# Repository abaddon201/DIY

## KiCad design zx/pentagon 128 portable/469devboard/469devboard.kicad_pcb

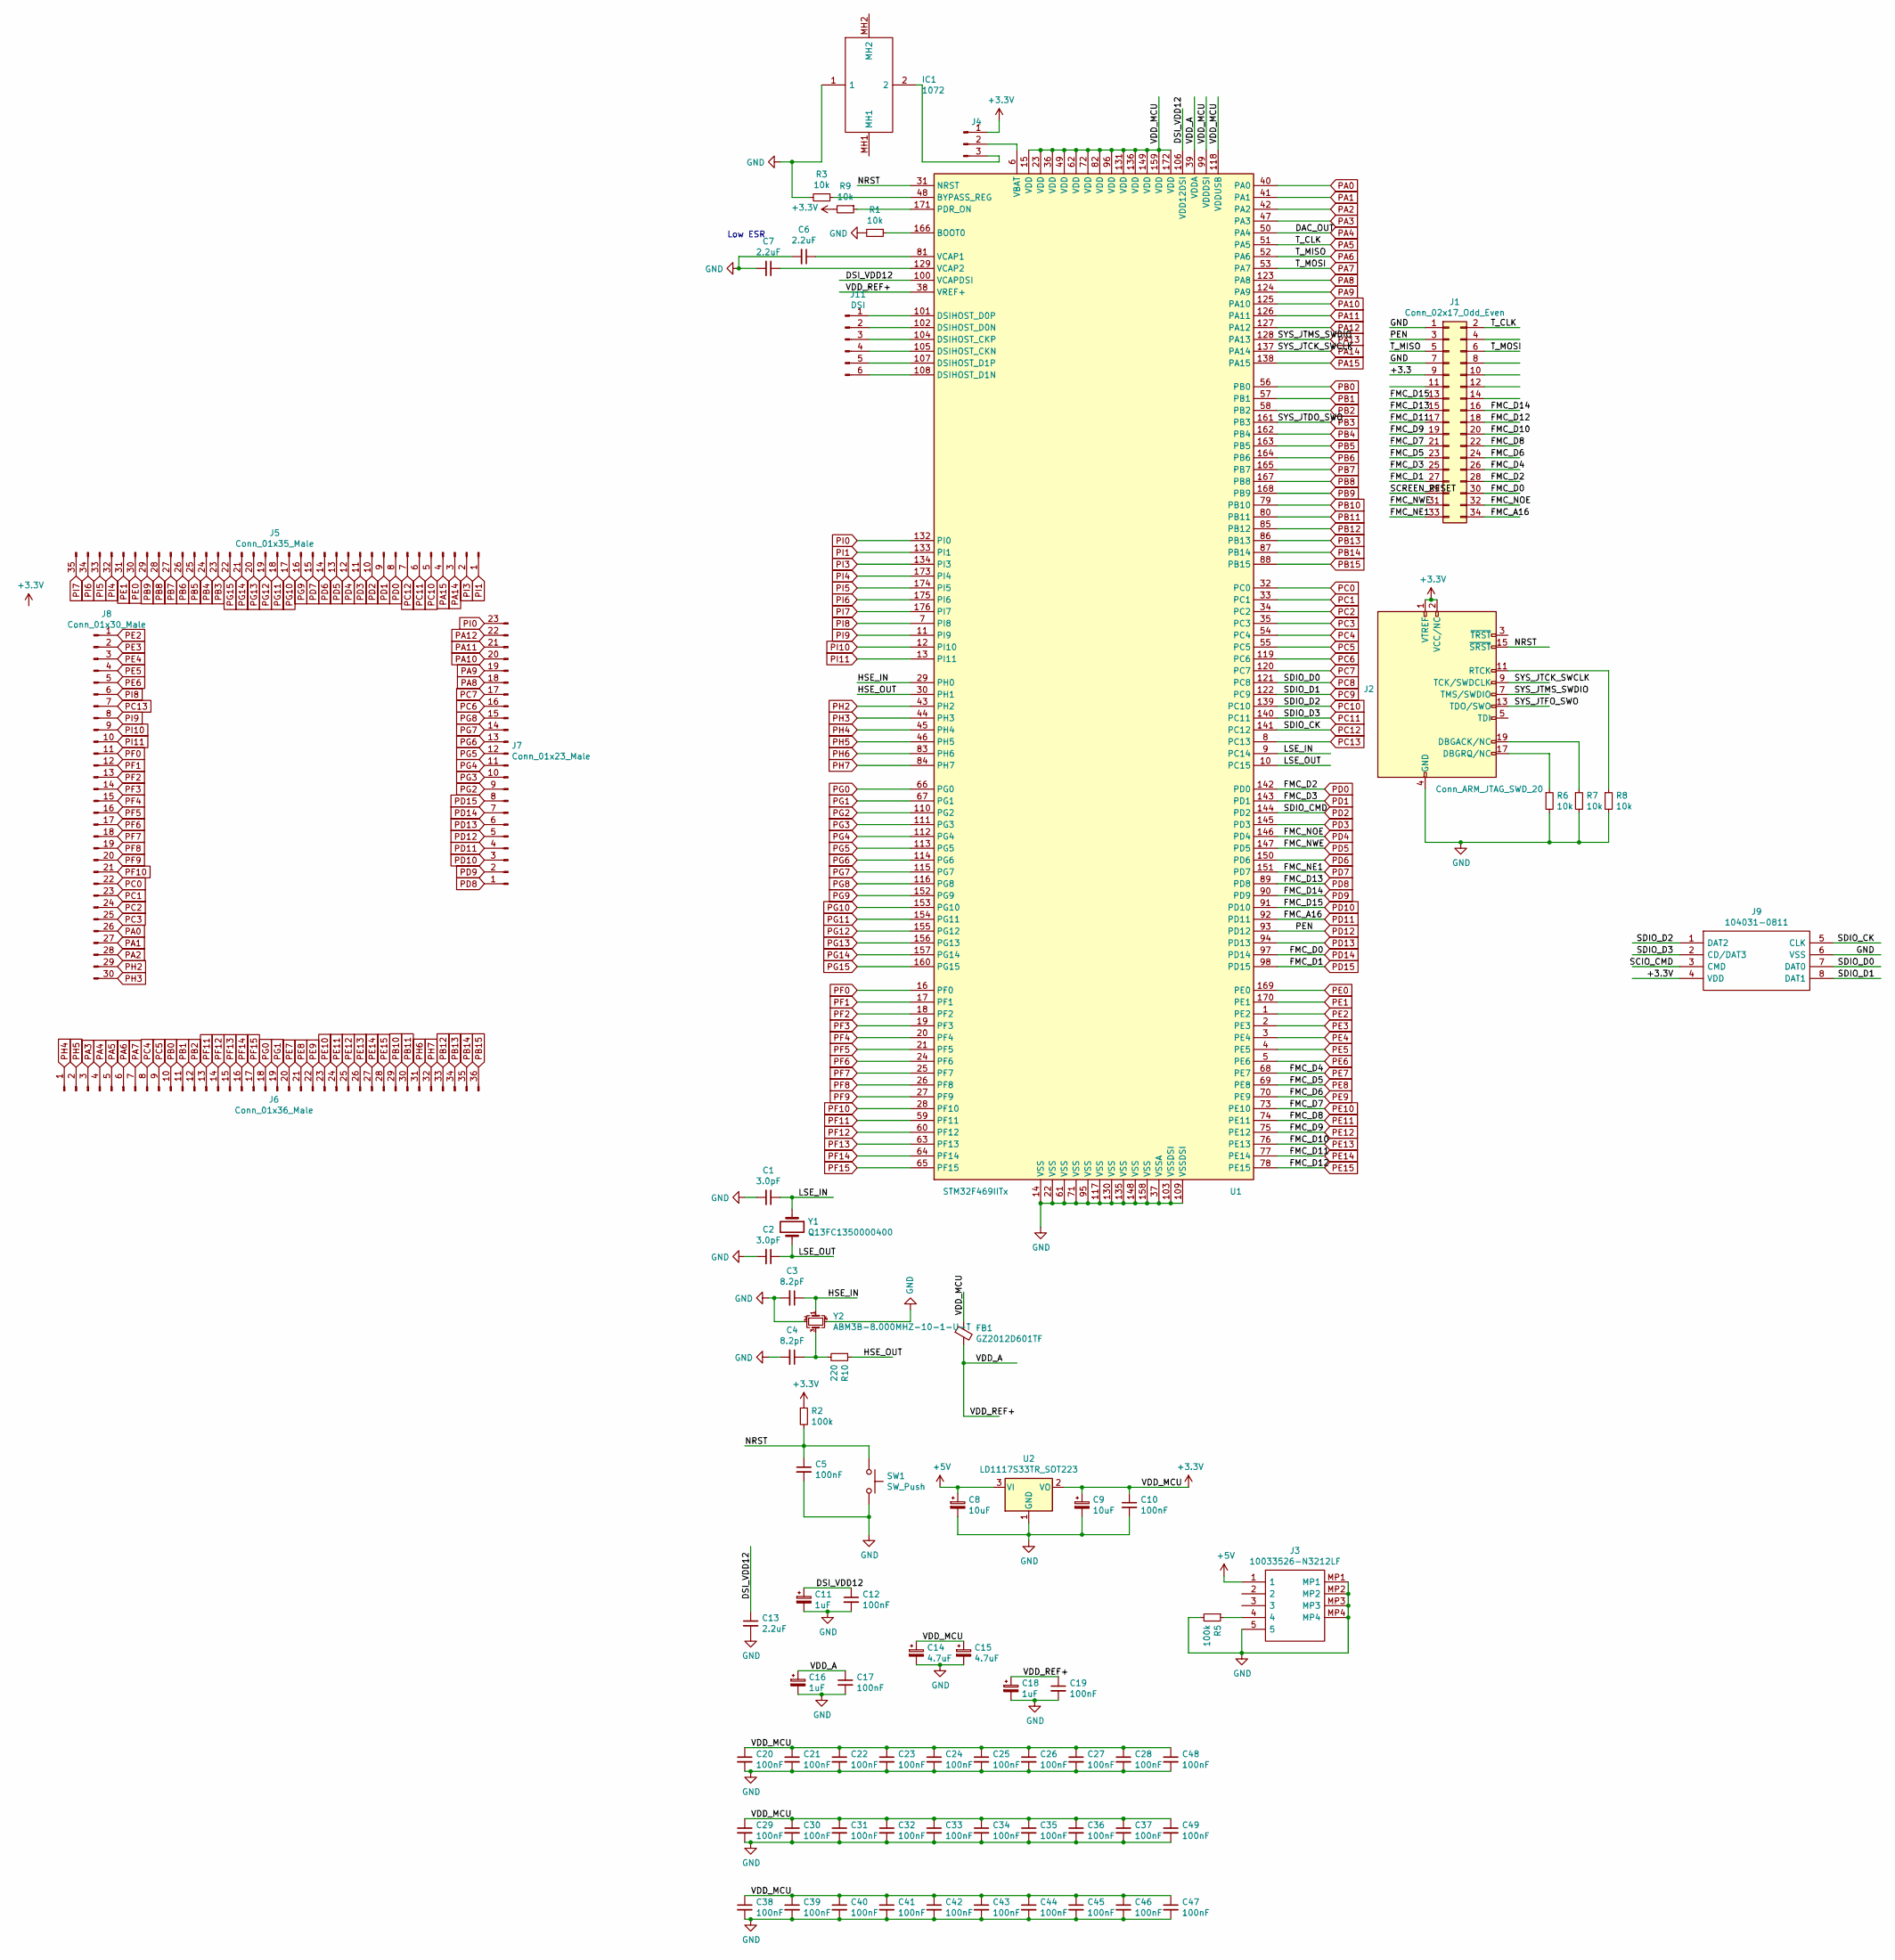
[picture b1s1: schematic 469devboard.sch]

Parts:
C1, C2: 3.0pF; C_0402_1005Metric
C3, C4: 8.2pF; C_0402_1005Metric
C5, C10, C12, C17, C19, C20, C21, C22, C23, C24, C25, C26, C27, C28, C29, C30, C31, C32, C33, C34, C35, C36, C37, C38, C39, C40, C41, C42, C43, C44, C45, C46, C47, C48, C49: 100nF; C_0402_1005Metric
C6, C7: 2.2uF; C_1210_3225Metric_Pad1.42x2.65mm_HandSolder
C8, C9: 10uF; C_0402_1005Metric
C11, C16, C18: 1uF; C_0402_1005Metric
C13: 2.2uF; C_0402_1005Metric
C14, C15: 4.7uF; C_0402_1005Metric
FB1: GZ2012D601TF; C_0805_2012Metric
IC1: 1072; Mouser Part Number 534-1072
J1: Conn_02x17_Odd_Even; PinSocket_2x17_P2.54mm_Vertical
J2: Conn_ARM_JTAG_SWD_20; PinHeader_2x10_P2.54mm_Vertical
J3: 10033526-N3212LF; 10033526N3212LF; Mouser Part Number 649-10033526-N3212LF
J4: Conn_01x03_Male; PinHeader_1x03_P2.54mm_Vertical
J5: Conn_01x35_Male; PinHeader_1x35_P2.54mm_Vertical
J6: Conn_01x36_Male; PinHeader_1x36_P2.54mm_Vertical
J7: Conn_01x23_Male; PinHeader_1x23_P2.54mm_Vertical
J8: Conn_01x30_Male; PinHeader_1x30_P2.54mm_Vertical
J9: 104031-0811; 1040310811; Mouser Part Number 538-104031-0811
J11: DSI; PinHeader_1x06_P2.54mm_Vertical
R1, R3, R6, R7, R8, R9: 10k; R_0402_1005Metric
R2, R5: 100k; R_0402_1005Metric
R10: 220; R_0402_1005Metric
SW1: SW_Push; SW_DIP_SPSTx01_Slide_6.7x4.1mm_W6.73mm_P2.54mm_LowProfile_J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
U1: STM32F469IITx; LQFP-176_24x24mm_P0.5mm
U2: LD1117S33TR_SOT223; SOT-223-3_TabPin2
Y1: Q13FC1350000400; Crystal_SMD_G8-2Pin_3.2x1.5mm
Y2: ABM3B-8.000MHZ-10-1-U-T; Crystal_SMD_Abracon_ABM3B-4Pin_5.0x3.2mm

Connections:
+3V3: C9.1, C10.1, C14.1, C15.1, C20.1, C21.1, C22.1, C23.1, C24.1, C25.1, C26.1, C27.1, C28.1, C29.1, C30.1, C31.1, C32.1, C33.1, C34.1, C35.1, C36.1, C37.1, C38.1, C39.1, C40.1, C41.1, C42.1, C43.1, C44.1, C45.1, C46.1, C47.1, C48.1, C49.1, FB1.1, J2.1 (VTREF), J2.2 (VCC/NC), J4.1, R2.1, R9.2, U1.15 (VDD), U1.23 (VDD), U1.36 (VDD), U1.49 (VDD), U1.62 (VDD), U1.72 (VDD), U1.82 (VDD), U1.96 (VDD), U1.99 (VDDDSI), U1.118 (VDDUSB), U1.131 (VDD), U1.136 (VDD), U1.149 (VDD), U1.159 (VDD), U1.172 (VDD), U2.2 (VO)
+5V: C8.1, J3.1, U2.3 (VI)
/DSI_VDD12: C11.1, C12.1, C13.1, U1.100 (VCAPDSI), U1.106 (VDD12DSI)
/HSE_IN: C3.1, U1.29 (PH0), Y2.1
/HSE_OUT: R10.1, U1.30 (PH1)
/LSE_IN: C1.1, U1.9 (PC14), Y1.1
/LSE_OUT: C2.1, U1.10 (PC15), Y1.2
/NRST: C5.1, J2.15 (~SRST~), R2.2, SW1.1, U1.31 (NRST)
/VDD_A: C16.1, C17.1, C18.1, C19.1, FB1.2, U1.38 (VREF+), U1.39 (VDDA)
GND: C1.2, C2.2, C3.2, C4.2, C5.2, C6.2, C7.2, C8.2, C9.2, C10.2, C11.2, C12.2, C13.2, C14.2, C15.2, C16.2, C17.2, C18.2, C19.2, C20.2, C21.2, C22.2, C23.2, C24.2, C25.2, C26.2, C27.2, C28.2, C29.2, C30.2, C31.2, C32.2, C33.2, C34.2, C35.2, C36.2, C37.2, C38.2, C39.2, C40.2, C41.2, C42.2, C43.2, C44.2, C45.2, C46.2, C47.2, C48.2, C49.2, IC1.1, J1.1, J1.7, J2.4 (GND), J2.6 (GND), J2.8 (GND), J2.10 (GND), J2.12 (GND), J2.14 (GND), J2.16 (GND), J2.18 (GND), J2.20 (GND), J3.5, J3.MP1, J3.MP2, J3.MP3, J3.MP4, J9.6 (VSS), R1.2, R3.2, R5.2, R6.2, R7.2, R8.2, SW1.2, U1.14 (VSS), U1.22 (VSS), U1.37 (VSSA), U1.61 (VSS), U1.71 (VSS), U1.95 (VSS), U1.103 (VSSDSI), U1.109 (VSSDSI), U1.117 (VSS), U1.130 (VSS), U1.135 (VSS), U1.148 (VSS), U1.158 (VSS), U2.1 (GND), Y2.2, Y2.4
unnamed: C4.1, R10.2, Y2.3
unnamed: C6.1, U1.81 (VCAP1)
unnamed: C7.1, U1.129 (VCAP2)
unnamed: IC1.2, J4.3
unnamed: J2.11 (RTCK), R8.1
unnamed: J2.17 (DBGRQ/NC), R6.1
unnamed: J2.19 (DBGACK/NC), R7.1
unnamed: J3.4, R5.1
unnamed: J4.2, U1.6 (VBAT)
unnamed: J11.1, U1.101 (DSIHOST_D0P)
unnamed: J11.2, U1.102 (DSIHOST_D0N)
unnamed: J11.3, U1.104 (DSIHOST_CKP)
unnamed: J11.4, U1.105 (DSIHOST_CKN)
unnamed: J11.5, U1.107 (DSIHOST_D1P)
unnamed: J11.6, U1.108 (DSIHOST_D1N)
unnamed: R1.1, U1.166 (BOOT0)
unnamed: R3.1, U1.48 (BYPASS_REG)
unnamed: R9.1, U1.171 (PDR_ON)
PA0: J8.26, U1.40 (PA0)
PA1: J8.27, U1.41 (PA1)
PA2: J8.28, U1.42 (PA2)
PA3: J6.3, U1.47 (PA3)
PA4: J6.4, U1.50 (PA4)
PA5: J1.2, J6.5, U1.51 (PA5)
PA6: J1.5, J6.6, U1.52 (PA6)
PA7: J1.6, J6.7, U1.53 (PA7)
PA8: J7.18, U1.123 (PA8)
PA9: J7.19, U1.124 (PA9)
PA10: J7.20, U1.125 (PA10)
PA11: J7.21, U1.126 (PA11)
PA12: J7.22, U1.127 (PA12)
PA13: J2.7 (TMS/SWDIO), U1.128 (PA13)
PA14: J2.9 (TCK/SWDCLK), J5.3, U1.137 (PA14)
PA15: J5.4, U1.138 (PA15)
PB0: J6.10, U1.56 (PB0)
PB1: J6.11, U1.57 (PB1)
PB2: J6.12, U1.58 (PB2)
PB3: J5.23, U1.161 (PB3)
PB4: J5.24, U1.162 (PB4)
PB5: J5.25, U1.163 (PB5)
PB6: J5.26, U1.164 (PB6)
PB7: J5.27, U1.165 (PB7)
PB8: J5.28, U1.167 (PB8)
PB9: J5.29, U1.168 (PB9)
PB10: J6.29, U1.79 (PB10)
PB11: J6.30, U1.80 (PB11)
PB12: J6.33, U1.85 (PB12)
PB13: J6.34, U1.86 (PB13)
PB14: J6.35, U1.87 (PB14)
PB15: J6.36, U1.88 (PB15)
PC0: J8.22, U1.32 (PC0)
PC1: J8.23, U1.33 (PC1)
PC2: J8.24, U1.34 (PC2)
PC3: J8.25, U1.35 (PC3)
PC4: J6.8, U1.54 (PC4)
PC5: J6.9, U1.55 (PC5)
PC6: J7.16, U1.119 (PC6)
PC7: J7.17, U1.120 (PC7)
PC8: J9.7 (DAT0), U1.121 (PC8)
PC9: J9.8 (DAT1), U1.122 (PC9)
PC10: J5.5, J9.1 (DAT2), U1.139 (PC10)
PC11: J5.6, J9.2 (CD/DAT3), U1.140 (PC11)
PC12: J5.7, J9.5 (CLK), U1.141 (PC12)
PC13: J8.7, U1.8 (PC13)
PD0: J1.28, J5.8, U1.142 (PD0)
PD1: J1.25, J5.9, U1.143 (PD1)
PD2: J5.10, U1.144 (PD2)
PD3: J5.11, U1.145 (PD3)
PD4: J1.32, J5.12, U1.146 (PD4)
PD5: J1.31, J5.13, U1.147 (PD5)
PD6: J5.14, U1.150 (PD6)
PD7: J1.33, J5.15, U1.151 (PD7)
PD8: J1.15, J7.1, U1.89 (PD8)
PD9: J1.16, J7.2, U1.90 (PD9)
PD10: J1.13, J7.3, U1.91 (PD10)
PD11: J1.34, J7.4, U1.92 (PD11)
PD12: J1.3, J7.5, U1.93 (PD12)
PD13: J7.6, U1.94 (PD13)
PD14: J1.30, J7.7, U1.97 (PD14)
PD15: J1.27, J7.8, U1.98 (PD15)
PE0: J5.30, U1.169 (PE0)
PE1: J5.31, U1.170 (PE1)
PE2: J8.1, U1.1 (PE2)
PE3: J8.2, U1.2 (PE3)
PE4: J8.3, U1.3 (PE4)
PE5: J8.4, U1.4 (PE5)
PE6: J8.5, U1.5 (PE6)
PE7: J1.26, J6.20, U1.68 (PE7)
PE8: J1.23, J6.21, U1.69 (PE8)
PE9: J1.24, J6.22, U1.70 (PE9)
PE10: J1.21, J6.23, U1.73 (PE10)
PE11: J1.22, J6.24, U1.74 (PE11)
PE12: J1.19, J6.25, U1.75 (PE12)
PE13: J1.20, J6.26, U1.76 (PE13)
PE14: J1.17, J6.27, U1.77 (PE14)
PE15: J1.18, J6.28, U1.78 (PE15)
PF0: J8.11, U1.16 (PF0)
PF1: J8.12, U1.17 (PF1)
PF2: J8.13, U1.18 (PF2)
PF3: J8.14, U1.19 (PF3)
PF4: J8.15, U1.20 (PF4)
PF5: J8.16, U1.21 (PF5)
PF6: J8.17, U1.24 (PF6)
PF7: J8.18, U1.25 (PF7)
PF8: J8.19, U1.26 (PF8)
PF9: J8.20, U1.27 (PF9)
PF10: J8.21, U1.28 (PF10)
PF11: J6.13, U1.59 (PF11)
PF12: J6.14, U1.60 (PF12)
PF13: J6.15, U1.63 (PF13)
PF14: J6.16, U1.64 (PF14)
PF15: J6.17, U1.65 (PF15)
PG0: J6.18, U1.66 (PG0)
PG1: J6.19, U1.67 (PG1)
PG2: J7.9, U1.110 (PG2)
PG3: J7.10, U1.111 (PG3)
PG4: J7.11, U1.112 (PG4)
PG5: J7.12, U1.113 (PG5)
PG6: J7.13, U1.114 (PG6)
PG7: J7.14, U1.115 (PG7)
PG8: J7.15, U1.116 (PG8)
PG9: J5.16, U1.152 (PG9)
PG10: J5.17, U1.153 (PG10)
PG11: J5.18, U1.154 (PG11)
PG12: J5.19, U1.155 (PG12)
PG13: J5.20, U1.156 (PG13)
PG14: J5.21, U1.157 (PG14)
PG15: J5.22, U1.160 (PG15)
PH2: J8.29, U1.43 (PH2)
PH3: J8.30, U1.44 (PH3)
PH4: J6.1, U1.45 (PH4)
PH5: J6.2, U1.46 (PH5)
PH6: J6.31, U1.83 (PH6)
PH7: J6.32, U1.84 (PH7)
PI0: J7.23, U1.132 (PI0)
PI1: J5.1, U1.133 (PI1)
PI3: J5.2, U1.134 (PI3)
PI4: J5.32, U1.173 (PI4)
PI5: J5.33, U1.174 (PI5)
PI6: J5.34, U1.175 (PI6)
PI7: J5.35, U1.176 (PI7)
PI8: J8.6, U1.7 (PI8)
PI9: J8.8, U1.11 (PI9)
PI10: J8.9, U1.12 (PI10)
PI11: J8.10, U1.13 (PI11)

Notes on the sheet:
Low ESR

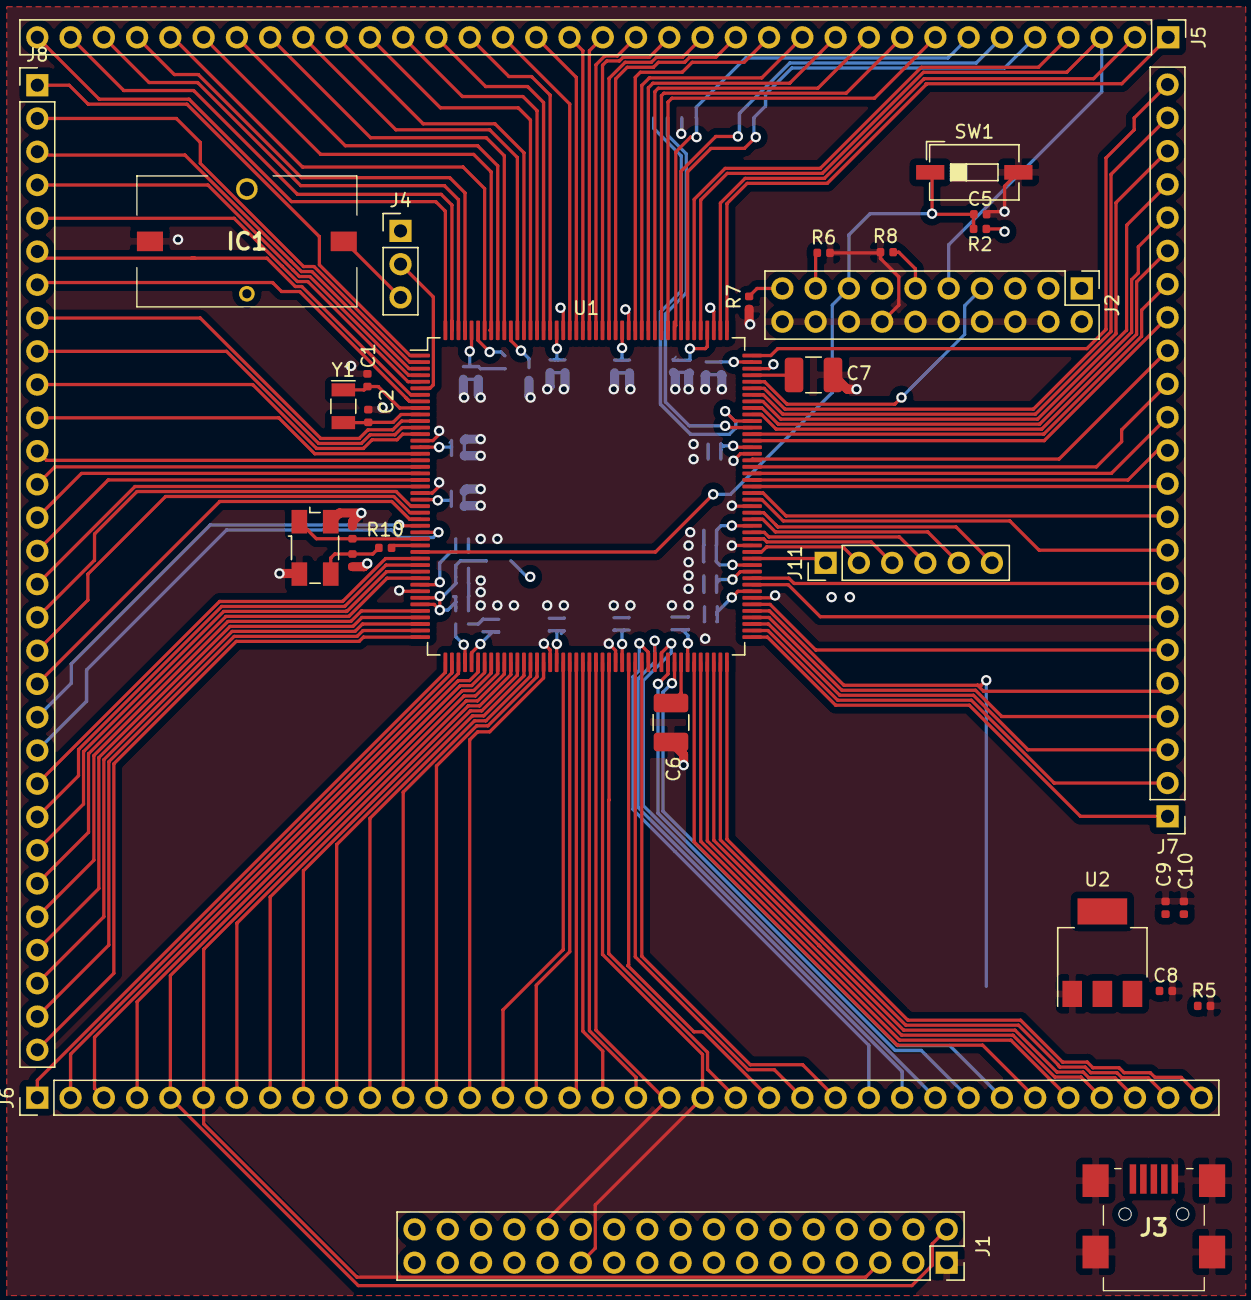
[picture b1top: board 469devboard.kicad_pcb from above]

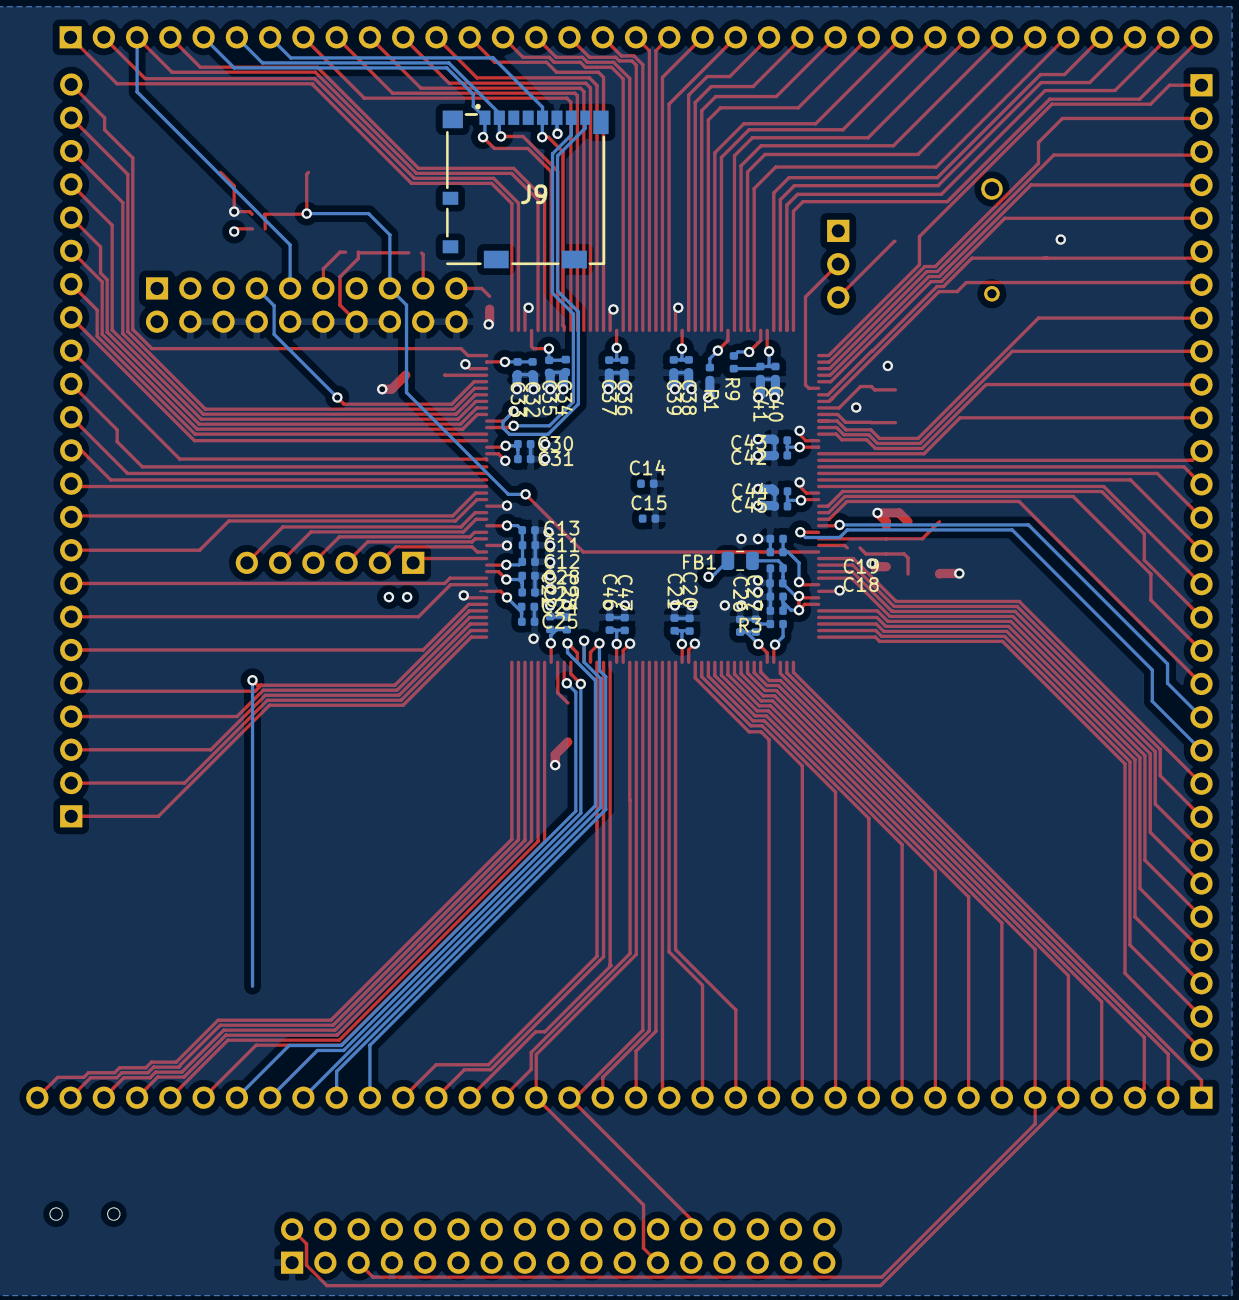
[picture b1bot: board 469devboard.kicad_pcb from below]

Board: 4 copper layers, 75 parts (44 on the bottom side), 155 nets.

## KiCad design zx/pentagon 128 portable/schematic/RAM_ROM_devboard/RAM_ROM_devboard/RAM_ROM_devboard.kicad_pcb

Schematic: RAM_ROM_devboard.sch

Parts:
C1: C_Small; C_0402_1005Metric
IC1: IS62C1024AL-35QLI; SOIC127P1412X305-32N; Mouser Part Number 870IS62C1024AL35QLI
IC2: SN74AHCT04D; SOIC127P600X175-14N; Mouser Part Number 595-SN74AHCT04D
J1: Conn_02x14_Odd_Even; PinHeader_2x14_P2.54mm_Vertical
J2: 8432-11B1-RK-TP; 843211B1RKTP; Mouser Part Number 517-8432-11B1-RK-TP
J3: Conn_02x08_Odd_Even; PinHeader_2x08_P2.54mm_Vertical
J4: Conn_02x04_Odd_Even; PinHeader_2x04_P2.54mm_Vertical
J5, J6: Conn_02x06_Odd_Even; PinHeader_2x06_P2.54mm_Vertical

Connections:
+5V: C1.1, IC1.32 (VDD), IC2.3 (2A), IC2.5 (3A), IC2.9 (4A), IC2.11 (5A), IC2.13 (6A), IC2.14 (VCC), J2.32, J4.2, J4.4, J4.6, J4.8
/A0: IC1.12 (A0), J1.1, J1.2, J2.12
/A1: IC1.11 (A1), J1.3, J1.4, J2.11
/A2: IC1.10 (A2), J1.5, J1.6, J2.10
/A3: IC1.9 (A3), J1.7, J1.8, J2.9
/A4: IC1.8 (A4), J1.9, J1.10, J2.8
/A5: IC1.7 (A5), J1.11, J1.12, J2.7
/A6: IC1.6 (A6), J1.13, J1.14, J2.6
/A7: IC1.5 (A7), J1.15, J1.16, J2.5
/A8: IC1.27 (A8), J1.17, J1.18, J2.27
/A9: IC1.26 (A9), J1.19, J1.20, J2.26
/A10: IC1.23 (A10), J1.21, J1.22, J2.23
/A11: IC1.25 (A11), J1.23, J1.24, J2.25
/A12: IC1.4 (A12), J1.25, J1.26, J2.4
/A13: IC1.28 (A13), J1.27, J1.28, J2.28
/D0: IC1.13 (I/O0), J2.13, J3.1, J3.2
/D1: IC1.14 (I/O1), J2.14, J3.3, J3.4
/D2: IC1.15 (I/O2), J2.15, J3.5, J3.6
/D3: IC1.17 (I/O3), J2.17, J3.7, J3.8
/D4: IC1.18 (I/O4), J2.18, J3.9, J3.10
/D5: IC1.19 (I/O5), J2.19, J3.11, J3.12
/D6: IC1.20 (I/O6), J2.20, J3.13, J3.14
/D7: IC1.21 (I/O7), J2.21, J3.15, J3.16
/RAM_A14: IC1.3 (A14), J5.1, J5.2
/RAM_A15: IC1.31 (A15), J5.3, J5.4
/RAM_A16: IC1.2 (A16), J5.5, J5.6
/RAM_CE: IC1.30 (CE2), IC2.2 (1Y)
/ROM_A14: J2.29, J6.1, J6.2
/ROM_A15: J2.3, J6.3, J6.4
/ROM_A16: J2.2, J6.5, J6.6
/~RAM_CE: IC1.22 (~CE1), IC2.1 (1A), J5.9, J5.10
/~RAM_OE: IC1.24 (~OE), J5.7, J5.8
/~RAM_WE: IC1.29 (~WE), J5.11, J5.12
/~ROM_CE: J2.22, J6.9, J6.10
/~ROM_OE: J2.24, J6.7, J6.8
/~ROM_WE: J2.31, J6.11, J6.12
GND: C1.2, IC1.16 (GND), IC2.7 (GND), J2.16, J4.1, J4.3, J4.5, J4.7

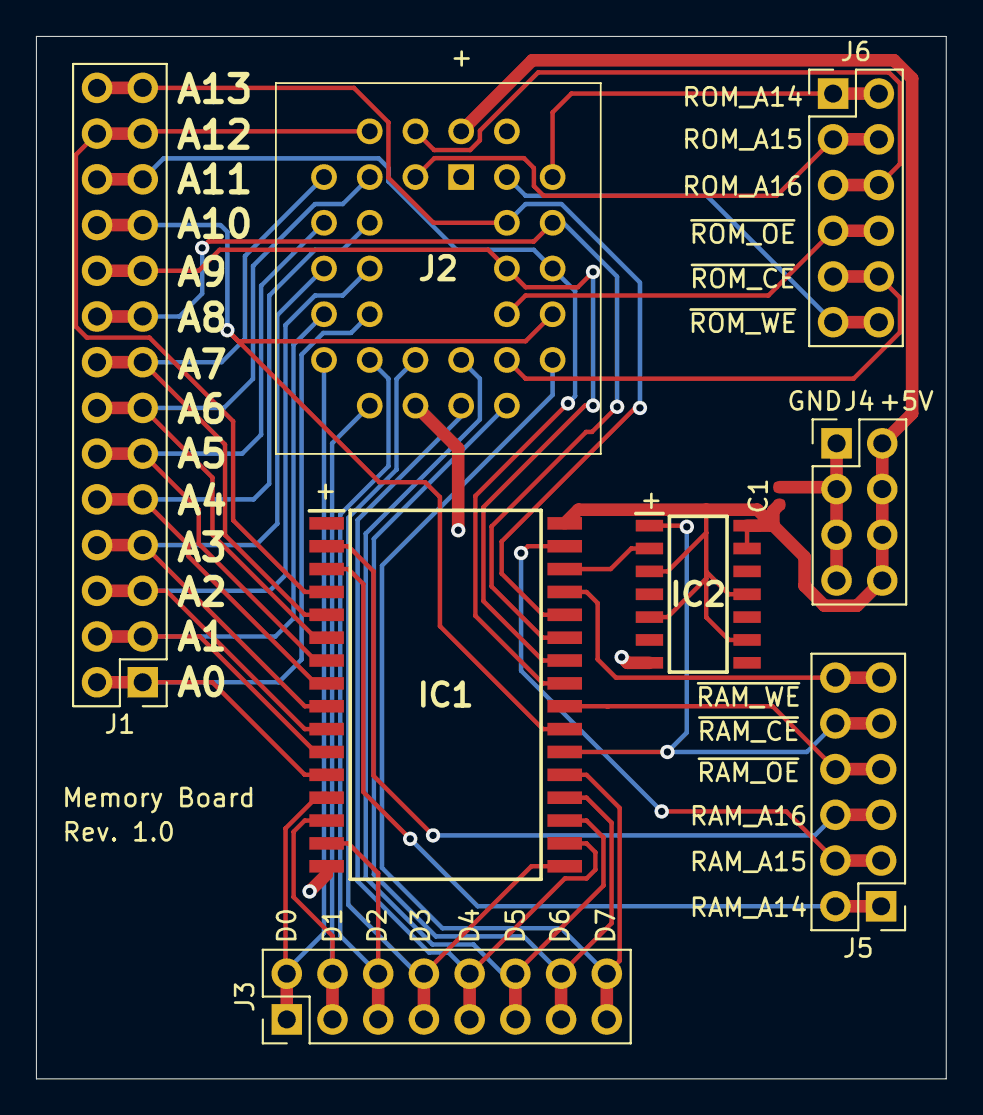
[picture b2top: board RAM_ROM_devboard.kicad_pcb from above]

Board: 2 copper layers, 50.5 x 57.9 mm, 9 parts (0 on the bottom side), 37 nets.
